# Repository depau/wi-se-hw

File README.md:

# Wi-Se (Hardware)

Wi-Se is a set of ESP8266-based boards intended to be used with
[Wi-Se (firmware)](https://github.com/Depau/wi-se-sw/).

They are intended to be always connected to a device's UART header in order to
troubleshoot boot issues or crashes without having to take the board out of the
case.

## Variants

### Rewirable

Provides solder jumpers to configure the header output. It can be powered from
5V or 3.3V.

### Raspberry Pi header

Compatible with Raspberry Pi and all boards with a compatible pinout.
Runs on 5V.

### Orange Pi 4 header

Orange Pi boards have a raspi header, however the main UART is usually on 3
separate pins.

This makes connection a little more awkward, since there's no power on the UART
header and they tend to orient it differently in different boards.

In fact, this variant has been designed to fit above the PCB of the Orange Pi 4.
On an Orange Pi Zero it would work, but it would stick out from the side.

It needs a jumper wire in order to connect the 5V power line.

**Note:** *the rendering above shows a straight male pin header for the bottom
connector. The rendering is just for demonstration purposes, a 90° male or
female header should be used instead, or a straight header but soldered on the
opposite side.*

## Revisions

### [v0.1](https://github.com/Depau/wi-se-hw/tree/v0.1)

Initial revision.

Issues:

- Missing pull-down resistor on GPIO15. Needs external resistor as can be seen
  in the pictures.
- Orange Pi 4 variant's BoM lists wrong LCSC part number for the UART resistors,
  ordering SMT assembly from JLC without correction results in UART data
  corruption. Schematics are correct.

### [v0.2](https://github.com/Depau/wi-se-hw/tree/v0.2)

Fixes the issues above.

## Specifications

The boards are stripped-down ESP8266 devkits that only perform voltage
regulation, UART communication, buttons for reset / bootloader mode, optional
headers for flashing with DTR/RTS (not tested).

The boards don't have a USB port. For initial flashing you need to connect it
to a UART adapter, then hold the GPIO0/IO0 button while pressing RESET. After
first flashing you can perform subsequent updates via Wi-Fi OTA.

## Ordering the boards

### Request assembled boards

While I do not sell the boards at the moment, I created a Google Form for people
who are interested: https://forms.gle/Le5gDNwtNsCusH8KA

This is not an order form: I will only order the boards if I get enough
requests.

Components will be ordered from China, so expect ~1 month from when I place the
order to when I will actually receive everything I need to assemble them.

### Make your own boards

The KiCad project files contain LCSC part numbers for ordering through JLCPCB.

PCB settings:

- Layers: 4
- Delivery format: single PCB
- Thickness: 1.6mm
- Color: green (SMT assembly is not available for other colors)
- Surface finish: HASL (other options are more expensive)
- Copper weight: 1 oz
- Remove order number: Specify a location (silkscreen contains JLC order number
  pattern under the ESP8266 footprint)
- Everything else set to defaults

BOM + position files compatible with JLC can be generated with the following
scripts: https://github.com/wokwi/kicad-jlcpcb-bom-plugin

If you request SMT assembly (100% recommended), please make sure the components
are aligned correctly. If they aren't you can edit the position file by hand
and correct the angle. JLC will also perform quality checks and ask your
confirmation if they notice potential issues.

The front side + tactile switches are not available on JLC's part list, so you
will have to order them separately and solder them manually.

I will provide AliExpress affiliate links once they approve my application, for
now this is the list of required components:

- ESP-WROOM-02 or ESP-WROOM-02D - 4MB flash preferred but not required
- 3x3x1.5mm SMD SPST tactile switch, 2x per board
- 0603 LEDs. Colors: 2x red, 1x amber/yellow, 1x blue.
  Current limiting resistors are tuned for these colors. If you prefer other
  colors you need to adjust the schematic.
- Pin headers, 2.54mm spacing. Type depends on your preference.

For Orange Pi 4 variant:
- 0603 1Kohm resistors, 2x per board
- 1206 10uF capacitors, 1x per board
- 1x3 pin female header, 2.54 spacing
- 1 pin 90° male header for VCC
- 1 female to female 5cm jumper cable

For Raspi variant:
- 0603 0 ohm resistor, 1x per board - **optional**
- 2x4 pin female header, 2.54mm spacing, 1x per board

For Rewirable variant:
- 1x4 pin header, 2.54mm, choose your own type based on the application

#### Cleaning the flux

I've noticed that flux tends to get under the ESP chip, glitching the board.
I would say that ultrasonic cleaning is required.

Link (with referral) for a cheap ultrasonic cleaner on Amazon.it:
https://amzn.to/38Vhwjc

## Assembly instructions

See `assembly-instructions.pdf`. The GPIO15 pull-down issue is solved in v0.2,
so unless you have a v0.1 board you don't need the external pull-down resistor.

## License

This project is licensed under the CERN Open Hardware License, Strictly
Reciprocal (CERN-OHL-S), version 2.

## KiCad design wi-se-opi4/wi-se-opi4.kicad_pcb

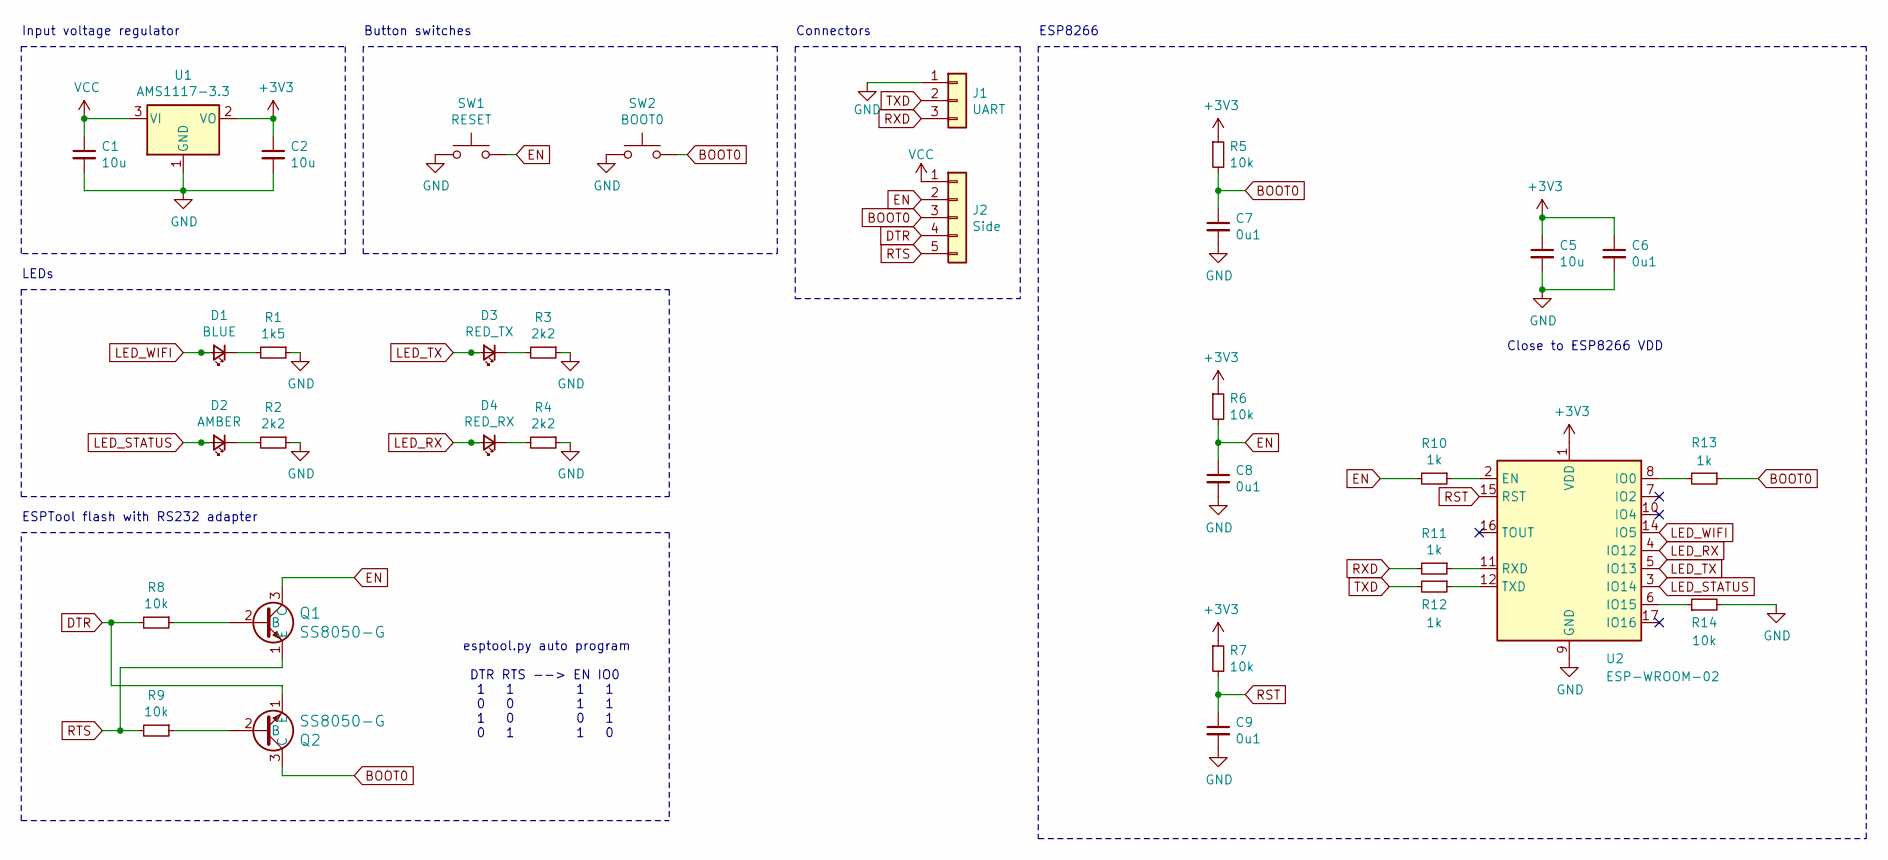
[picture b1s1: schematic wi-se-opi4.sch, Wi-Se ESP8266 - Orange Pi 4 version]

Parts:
C1: 10u; C_1206_3216Metric_Pad1.33x1.80mm_HandSolder; LCSC Part C13585
C2, C5: 10u; C_1206_3216Metric; LCSC Part C13585
C6: 0u1; C_0603_1608Metric; LCSC Part C14663
C7, C8, C9: 0u1; C_0402_1005Metric; LCSC Part C1546
D1: BLUE; LED_0603_1608Metric_Pad1.05x0.95mm_HandSolder
D2: AMBER; LED_0603_1608Metric_Pad1.05x0.95mm_HandSolder
D3: RED_TX; LED_0603_1608Metric_Pad1.05x0.95mm_HandSolder
D4: RED_RX; LED_0603_1608Metric_Pad1.05x0.95mm_HandSolder
J1: UART; PinSocket_1x03_P2.54mm_Vertical
J2: Side; PinHeader_1x05_P2.54mm_Vertical
Q1, Q2: SS8050-G; LCSC Part C2150
R1: 1k5; R_0402_1005Metric; LCSC Part C25867
R2, R3, R4: 2k2; R_0402_1005Metric; LCSC Part C25879
R5, R6, R7, R8, R9, R14: 10k; R_0402_1005Metric; LCSC Part C25744
R10, R13: 1k; R_0603_1608Metric_Pad0.98x0.95mm_HandSolder; LCSC Part C21190
R11, R12: 1k; R_0402_1005Metric; LCSC Part C11702
SW1: RESET; Tactile_Push_Button_SMD_3x3x1.5mm.kicad_mod
SW2: BOOT0; Tactile_Push_Button_SMD_3x3x1.5mm.kicad_mod
U1: AMS1117-3.3; SOT-223-3_TabPin2; LCSC Part C6186
U2: ESP-WROOM-02

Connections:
+3V3: C2.1, C5.1, C6.1, R5.1, R6.1, R7.1, U1.2 (VO), U2.1 (VDD)
BOOT0: C7.1, J2.3, Q2.3 (C), R5.2, R13.1, SW2.2
DTR: J2.4, Q2.1 (E), R8.2
EN: C8.1, J2.2, Q1.3 (C), R6.2, R10.2, SW1.2
GND: C1.2, C2.2, C5.2, C6.2, C7.2, C8.2, C9.2, J1.1, R1.1, R2.1, R3.1, R4.1, R14.2, SW1.1, SW2.1, U1.1 (GND), U2.9 (GND), U2.13 (GND), U2.18 (GND), U2.19 (GND)
LED_RX: D4.2 (A), U2.4 (IO12)
LED_STATUS: D2.2 (A), U2.3 (IO14)
LED_TX: D3.2 (A), U2.5 (IO13)
LED_WIFI: D1.2 (A), U2.14 (IO5)
unnamed: D1.1 (K), R1.2
unnamed: D2.1 (K), R2.2
unnamed: D3.1 (K), R3.2
unnamed: D4.1 (K), R4.2
unnamed: Q1.2 (B), R8.1
unnamed: Q2.2 (B), R9.1
unnamed: R10.1, U2.2 (EN)
unnamed: R11.1, U2.11 (RXD)
unnamed: R12.1, U2.12 (TXD)
unnamed: R13.2, U2.8 (IO0)
unnamed: R14.1, U2.6 (IO15)
RST: C9.1, R7.2, U2.15 (RST)
RTS: J2.5, Q1.1 (E), R9.2
RXD: J1.3, R11.2
TXD: J1.2, R12.2
VCC: C1.1, J2.1, U1.3 (VI)

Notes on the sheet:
Input voltage regulator
Button switches
LEDs
ESP8266
Connectors
ESPTool flash with RS232 adapter
esptool.py auto program DTR RTS --> EN IO0 1 1 1 1 0 0 1 1 1 0 0 1 0 1 1 0
Close to ESP8266 VDD

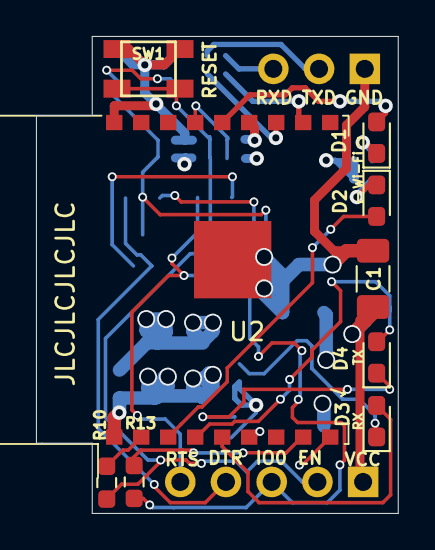
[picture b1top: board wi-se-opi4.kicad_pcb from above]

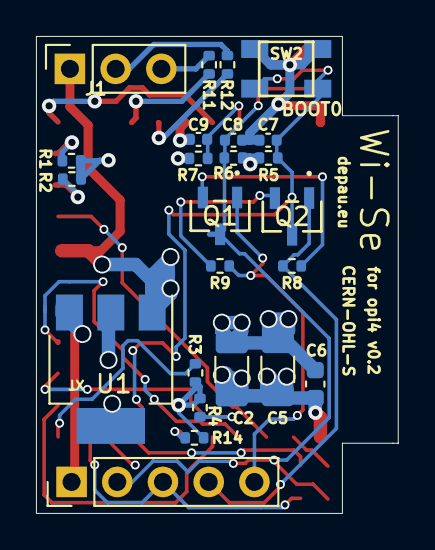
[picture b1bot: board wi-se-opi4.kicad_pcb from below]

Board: 4 copper layers, 20.1 x 26.5 mm, 33 parts (24 on the bottom side), 25 nets.

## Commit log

2021-01-14 Add LICENSE
2021-01-14 Rename files
2021-01-14 Add .gitignore
2021-01-16 Add libraries
2021-01-16 Add RasPi header version
2021-01-17 Make RPI version as small as it can be
2021-01-18 Add Boardview generator
2021-01-18 Final version of rpi variant (last famous words)
2021-01-18 Ground switch shields
2021-01-18 gitignore OpenBoardView database
2021-01-18 Update Opi4 version
2021-01-20 Add rewirable version
2021-01-20 Replace buttons with cheap aliexpress ones
2021-01-20 Remove expensive switch
2021-01-23 Fix rewirable board name in schematic
2021-03-19 opi4: Fix LCSC part number for UART resistors
2021-03-19 opi4: Add missing GPIO15 pull-down
2021-03-19 rpi: Add missing GPIO15 pull-down
2021-03-19 rewirable: Add missing GPIO15 pull-down
2021-03-19 Update version numbers on all documents
2021-03-19 Regenerate schematics and boardview
2021-03-19 all: Add tactile switches 3D model
2021-03-20 Add README and assembly instructions
2021-03-20 Update assembly instructions
